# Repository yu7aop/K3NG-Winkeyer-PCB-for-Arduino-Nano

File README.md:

# K3NG-Winkeyer-PCB-for-Arduino-Nano
K3NG Winkeyer PCB for Arduino Nano
Arduino KEYER by Eagle software.
PCB is toner-transfer method with hot Iron. 
I have a lot of dual pots and PCB is adjusted for it. 
If you are friendly with Eagle you can change footprint for any other pot's or you can import in other software.

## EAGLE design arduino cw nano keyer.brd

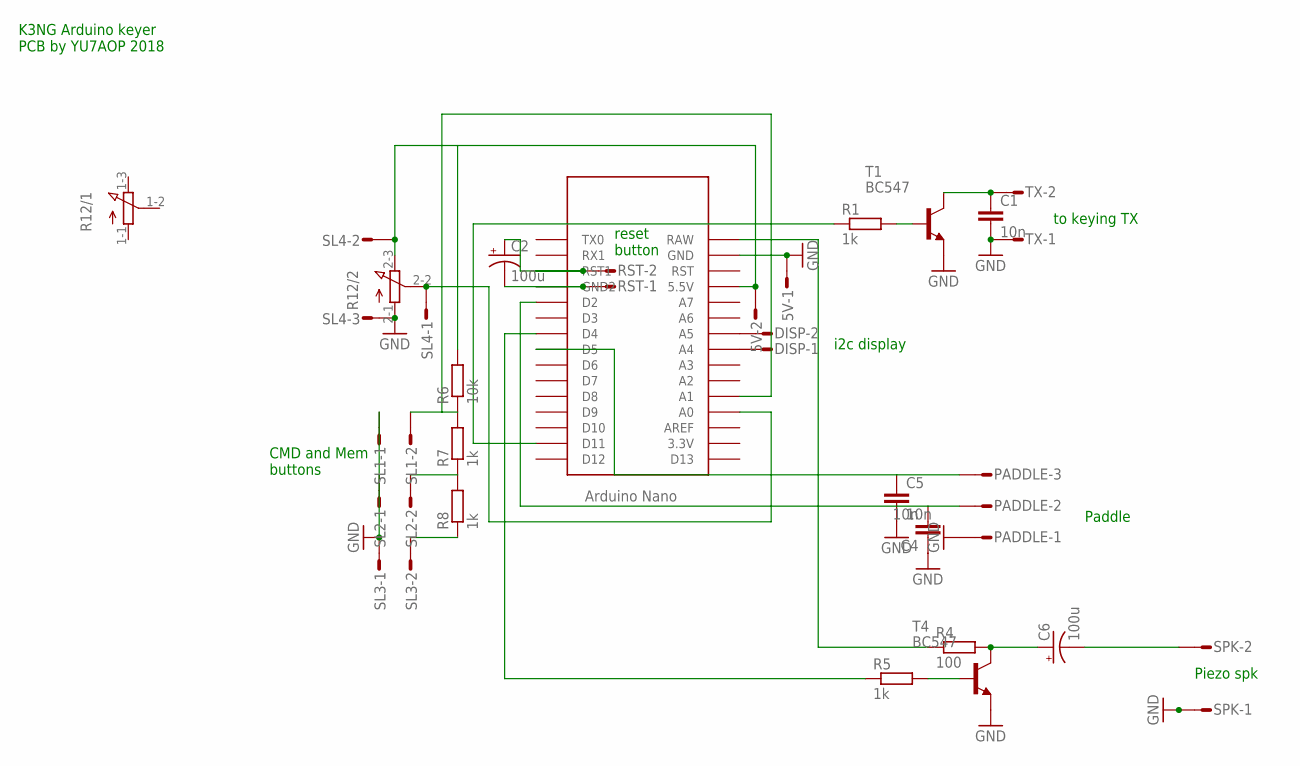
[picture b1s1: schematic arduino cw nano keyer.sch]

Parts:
5V: M02S; 02P
C1, C4, C5: 10n; C050-025X075
C2, C6: 100u; E2,5-5
DISP: M02S; 02P
PADDLE: M03S; 03P
R1, R5, R7, R8: 1k; 0207/10
R4: 100; 0207/10
R6: 10k; 0207/10
R12: 3RP/1610G
RST: M02S; 02P
SL1, SL2, SL3: M02S; 02P
SL4: M03S; 03P
SPK: M02S; 02P
T1, T4: BC547; TO92
TX: M02S; 02P
U$1: NANO

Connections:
GND: 5V.1, C1.2, C4.1, C5.2, PADDLE.1, R12.2-1 (A), SL1.1, SL2.1, SL3.1, SL4.3, SPK.1, T1.1 (E), T4.1 (E), TX.1, U$1.GND
unnamed: R6.1, R7.2, SL1.2, U$1.A1
unnamed: R7.1, R8.2, SL2.2
unnamed: R8.1, SL3.2
unnamed: C2.-, RST.1, U$1.GND1 (GND2)
unnamed: C2.+, RST.2, U$1.RST1
unnamed: R1.2, T1.2 (B)
unnamed: C1.1, T1.3 (C), TX.2
unnamed: DISP.2, U$1.A5
unnamed: DISP.1, U$1.A4
unnamed: R1.1, U$1.D11
unnamed: R5.2, T4.2 (B)
unnamed: C6.+, R4.2, T4.3 (C)
unnamed: 5V.2, R6.2, R12.2-3 (E), SL4.2, U$1.5V (5.5V)
unnamed: R5.1, U$1.D4
unnamed: R12.2-2 (S), SL4.1, U$1.A0
unnamed: C5.1, PADDLE.3, U$1.D5
unnamed: C4.2, PADDLE.2, U$1.D2
unnamed: C6.-, SPK.2
unnamed: R4.1, U$1.RAW

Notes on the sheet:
to keying TX
Paddle
Piezo spk
CMD and Mem buttons
i2c display
reset button
K3NG Arduino keyer PCB by YU7AOP 2018

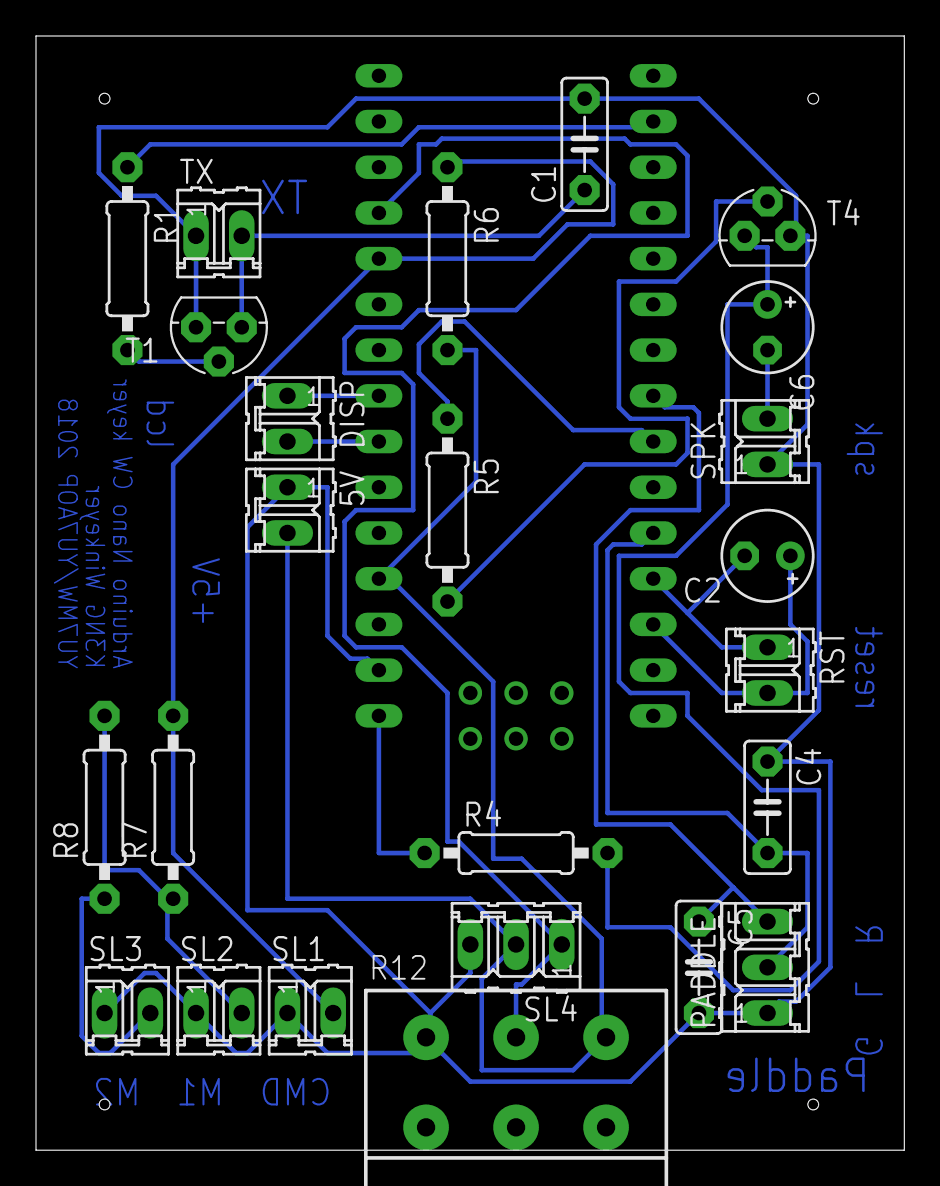
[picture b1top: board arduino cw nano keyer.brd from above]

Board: 2 copper layers, 48.2 x 61.9 mm, 25 parts (0 on the bottom side), 20 nets.

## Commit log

2018-11-06 Arduino CW keyer by K3NG
    Arduino KEYER by Eagle software.
    PCB is toner-transfer method with hot Iron. I have a lot of dual pots and PCB is adjusted for it. If you are friendly with Eagle you can change footprint for any other pot's or you can import in othe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
2018-11-06 K3NG Arduino keyer
    Arduino KEYER by Eagle software.
    PCB is toner-transfer method with hot Iron. I have a lot of dual pots and PCB is adjusted for it. If you are friendly with Eagle you can change footprint for any other pot's or you can import in othe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
